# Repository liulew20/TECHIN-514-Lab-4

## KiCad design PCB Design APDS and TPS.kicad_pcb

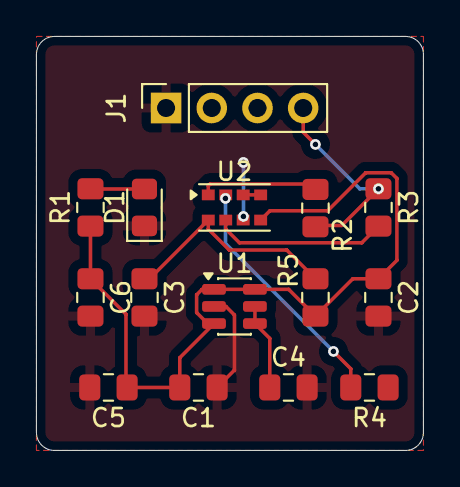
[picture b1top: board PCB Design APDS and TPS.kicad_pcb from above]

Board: 2 copper layers, 21.5 x 23.0 mm, 15 parts (0 on the bottom side), 10 nets.

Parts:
C1, C3: 1; C_0805_2012Metric_Pad1.18x1.45mm_HandSolder
C2: 10; C_0805_2012Metric_Pad1.18x1.45mm_HandSolder
C4: 0.01; C_0805_2012Metric_Pad1.18x1.45mm_HandSolder
C5: 0.1; C_0805_2012Metric_Pad1.18x1.45mm_HandSolder
C6: C; C_0805_2012Metric_Pad1.18x1.45mm_HandSolder
D1: LED; LED_0805_2012Metric_Pad1.15x1.40mm_HandSolder
J1: Conn_01x04_Pin; PinSocket_1x04_P2.54mm_Vertical
R1, R2, R3, R4: R; C_0805_2012Metric_Pad1.18x1.45mm_HandSolder
R5: 22; C_0805_2012Metric_Pad1.18x1.45mm_HandSolder
U1: TPS79301-EP; SOT-23-6
U2: APDS-9960; Avago_APDS-9960

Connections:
+3V3: C1.2, C2.1, C5.1, C6.1, R1.1, R5.1, U1.1 (IN), U1.3 (EN), U1.6 (OUT), U2.5 (LED_A)
+5V: J1.4, R2.1, R3.1
/SCL: R3.2, U2.7 (SCL)
/SDA: R2.2, U2.1 (SDA)
GND: C1.1, C2.2, C3.2, C4.2, C5.2, C6.2, D1.1 (K), J1.1, U1.2 (GND), U2.6 (GND)
unnamed: D1.2 (A), R1.2
unnamed: C4.1, U1.4 (BP), U1.5 (FB)
unnamed: R4.2, U2.2 (INT)
unnamed: U2.3 (LDR), U2.4 (LED_K)
unnamed: C3.1, R5.2, U2.8 (VDD)

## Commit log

2026-01-30 update lab 3
2026-01-30 update bom
